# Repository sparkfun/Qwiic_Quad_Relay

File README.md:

SparkFun Qwiic Quad Relay
========================================

[*SparkFun Qwiic Quad Relay (COM-16566)*](https://www.sparkfun.com/products/16566)

The Qwiic Quad Relay is a product designed for switching not one, but **four** high powered devices, from your Arduino or other low powered microcontroller using I<sup>2</sup>C. It's rocking four [relays](https://www.sparkfun.com/products/100) on its' PCB rated up to 5 Amps per channel at 250VAC. Each channel is sporting its own colored LED and silk for easy identification, and has screw terminals for easy connection.  

The board is made to integrate easily into the [Qwiic environment](https://www.sparkfun.com/qwiic) with Qwiic connectors on each side for easy daisy chaining. At the heart of the product is an ATtiny84 with its own I<sup>2</sup>C address awaiting for I<sup>2</sup>C commands that are designated to turn on and off individual channels or _all_ the channels at once! All of this is detailed nicely in provided example code, which also walks you through changing the boards single I<sup>2</sup>C address. There is a four pin header broken out for those of you not taking advantage of the Qwiic connector.

The onboard barrel jack is rated for wall warts in the range, 7-15V but there is a jumper on the underside in the case that your wall wart is 5V. Messing with such high voltage can be dangerous! We've included many safety precautions onto the PCB including, wide traces designed for high amperage, ground isolation between the relay and other circuitry, and a milled out area around the common pin of the relay.

Repository Contents
-------------------

* **/Firmware** - Latest firmware and examples. 
* **/Arduino Example** - Examples on how to use the product with buttons and switches, with hardware interrupts and without.
* **/Hardware** - Eagle design files (.brd, .sch)

Documentation
--------------

* **[Hookup Guide](https://learn.sparkfun.com/tutorials/qwiic-quad-relay-hookup-guide)** - Basic hookup guide

Arduino Library
--------------
* **[SparkFun Qwiic Relay Ardruino Library](https://github.com/sparkfun/SparkFun_Qwiic_Relay_Arduino_Library)** - SparkFun Arduino Library for controlling the Qwiic Single and Quad Relay

License Information
-------------------

This product is _**open source**_! 

Please review the LICENSE.md file for license information. 

If you have any questions or concerns on licensing, please contact technical support on our [SparkFun forums](https://forum.sparkfun.com/viewforum.php?f=152).

Please use, reuse, and modify these files as you see fit. Please maintain attribution to SparkFun Electronics and release under the same license.

Distributed as-is; no warranty is given.

- Your friends at SparkFun.

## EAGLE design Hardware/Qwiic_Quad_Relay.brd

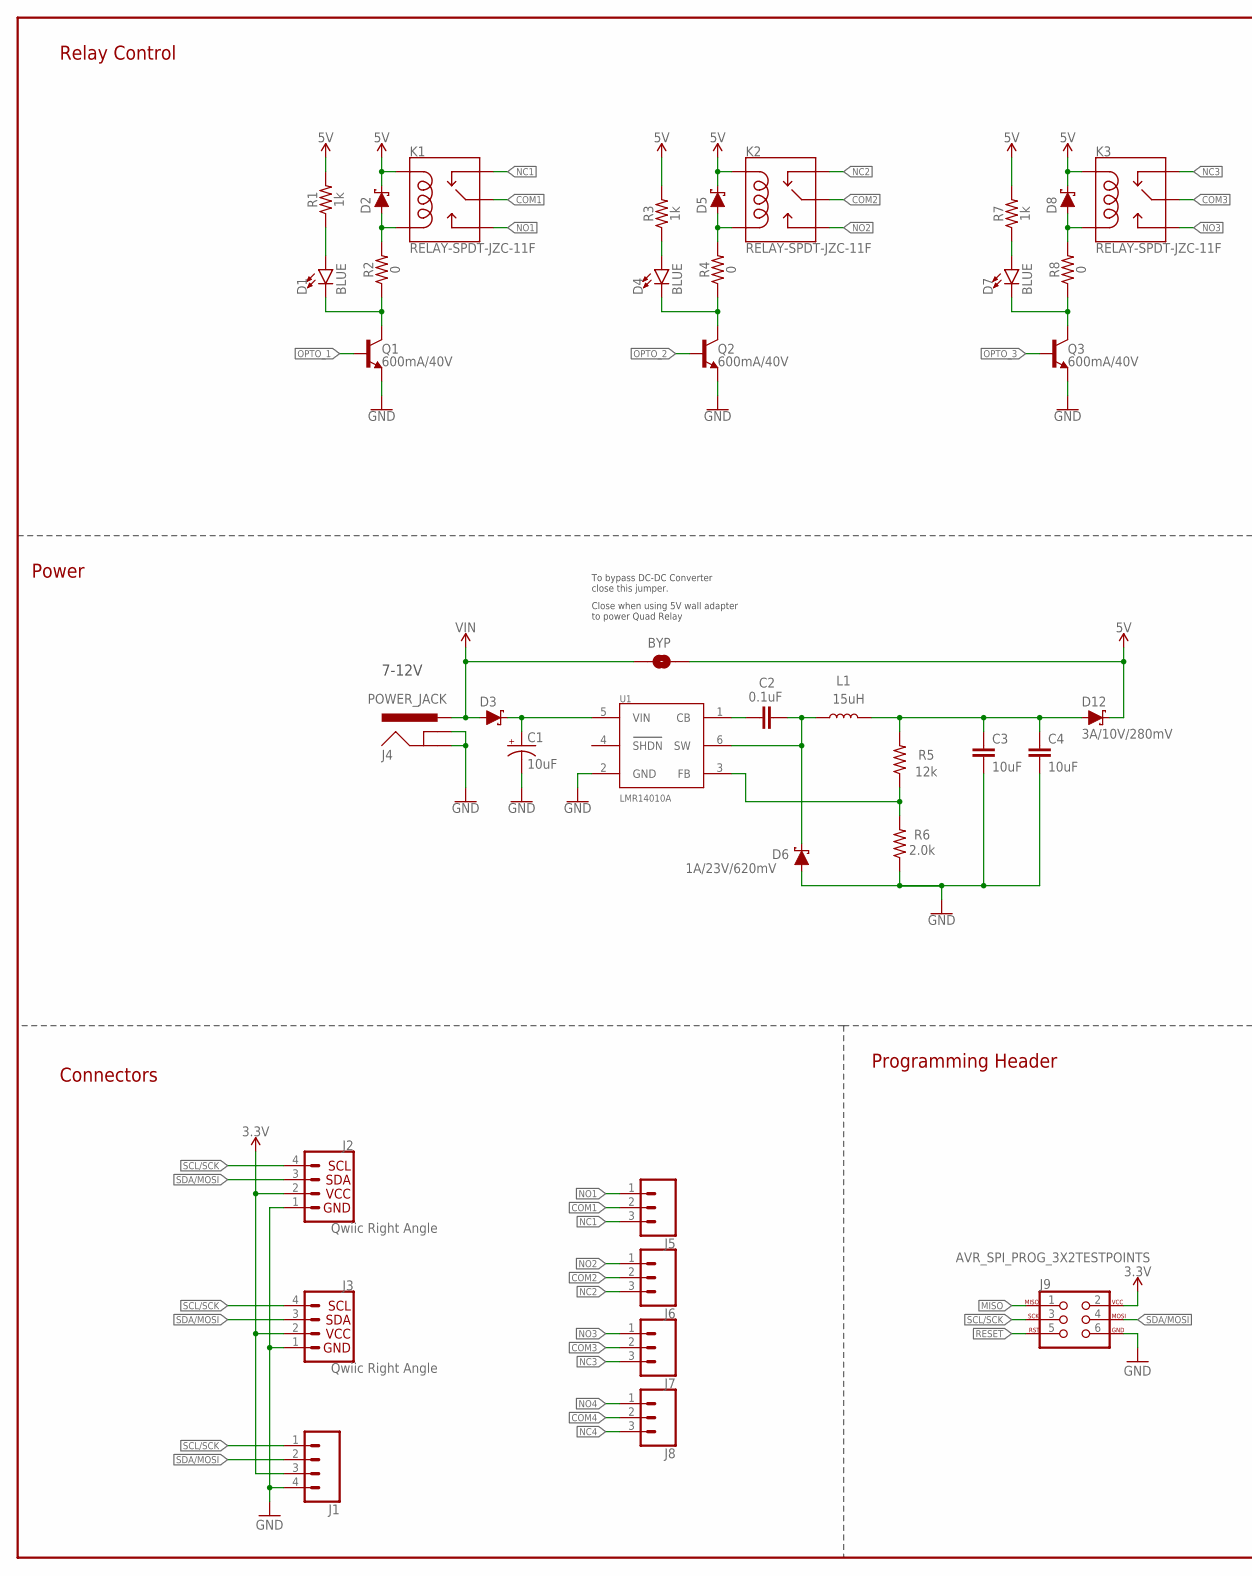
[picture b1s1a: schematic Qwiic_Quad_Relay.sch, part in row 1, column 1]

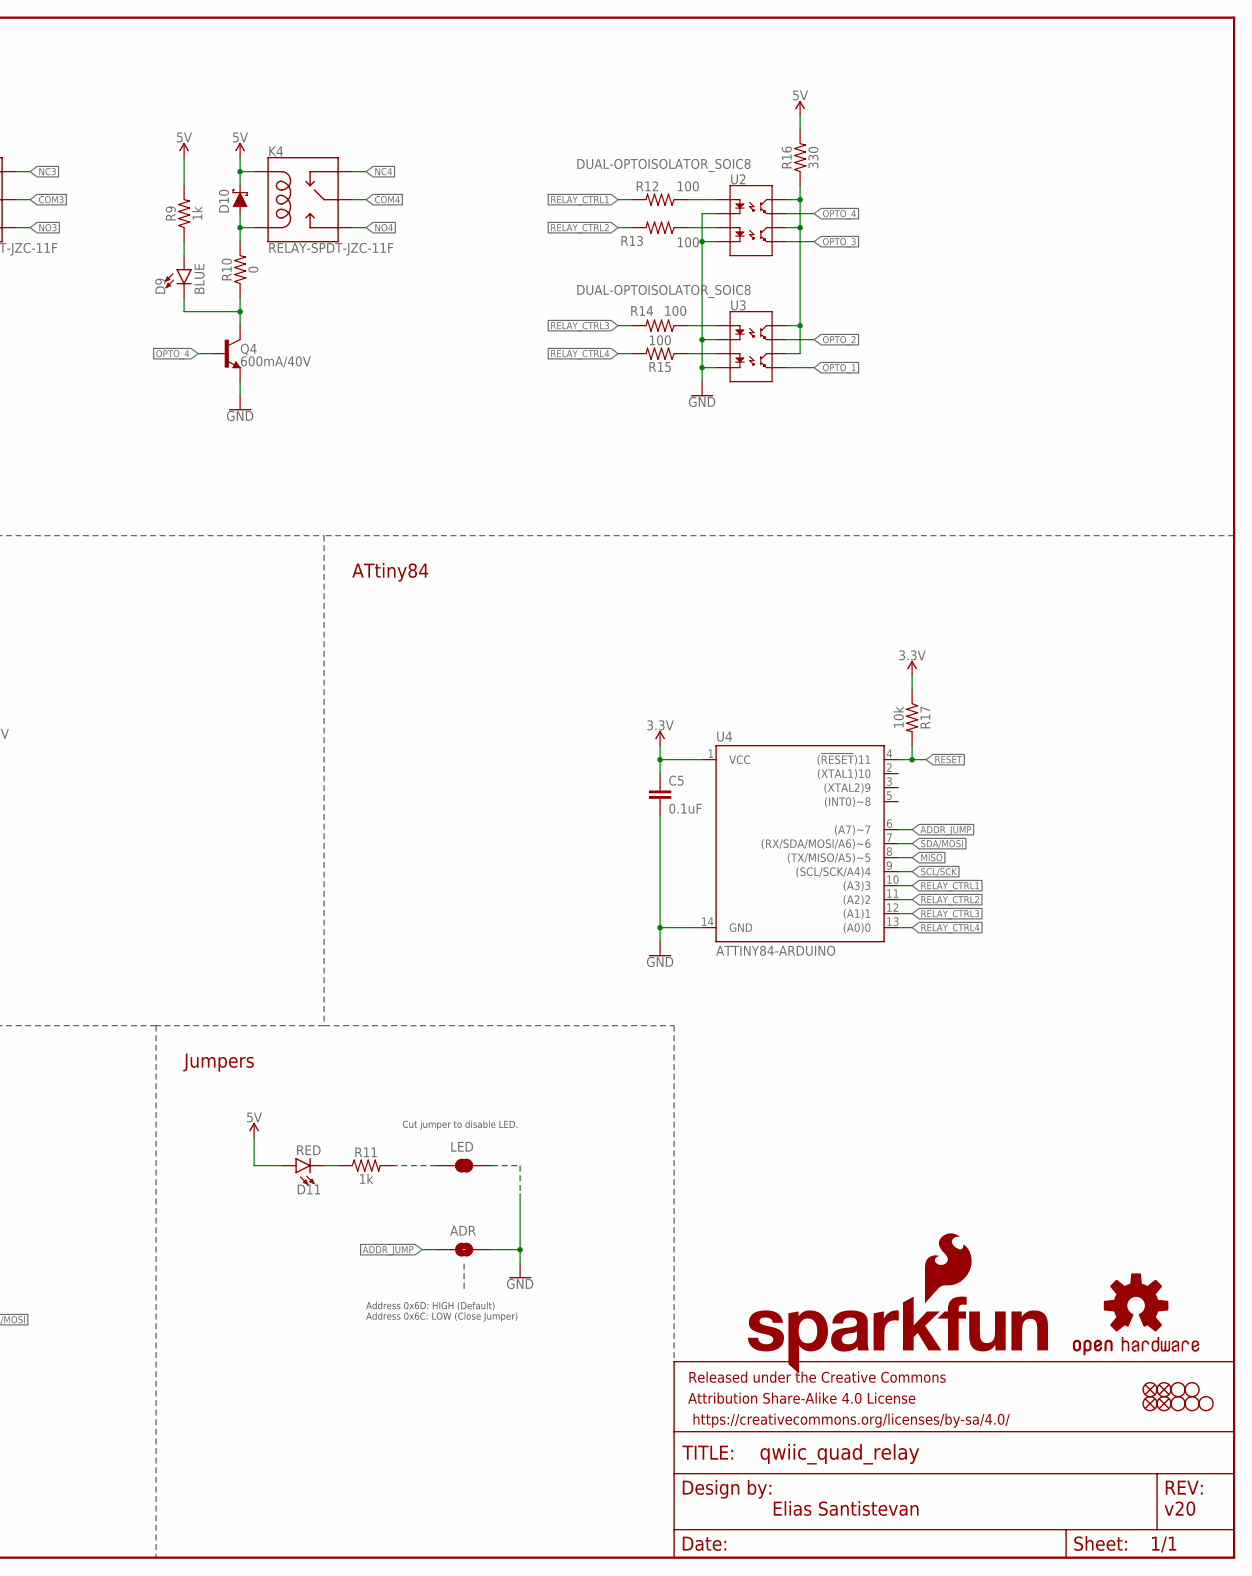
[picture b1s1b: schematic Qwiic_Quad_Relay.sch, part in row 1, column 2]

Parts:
ADR: JUMPER-SMT_2_NO_SILK; SMT-JUMPER_2_NO_SILK
BYP: JUMPER-SMT_2_NO_SILK; SMT-JUMPER_2_NO_SILK
C1: 10uF; EIA3528
C2: 0.1uF; 0402
C3, C4: 10uF; 0603
C5: 0.1uF; 0603
D1, D4, D7, D9: BLUE; LED-0603
D2, D5, D6, D8, D10: 1A/23V/620mV; SOD-323
D3: 1A/40V/500mV; SMA-DIODE
D11: RED; LED-0603
D12: 3A/10V/280mV; SOD-323
FD1, FD2, FD3, FD4: FIDUCIAL1X2; FIDUCIAL-1X2
FRAME1: FRAME-LEDGER; CREATIVE_COMMONS
J1: CONN_041X04_NO_SILK_NO_POP; 1X04_NO_SILK
J2, J3: Qwiic Right Angle; JST04_1MM_RA
J4: POWER_JACK; POWER_JACK_PTH
J5, J6, J7, J8: CONN_03-SCREW-5MM; SCREWTERMINAL-5MM-3
J9: AVR_SPI_PROG_3X2TESTPOINTS; 2X3_TEST_POINTS
JP1, JP4, JP5, JP6, JP7: STAND-OFF
K1, K2, K3, K4: RELAY-SPDT-JZC-11F; RELAY-JZC
L1: 15uH; INDUCTOR_15UH
LED: JUMPER-SMT_2_NC_TRACE_SILK; SMT-JUMPER_2_NC_TRACE_SILK
LOGO1: SFE_LOGO_NAME_FLAME.1_INCH; SFE_LOGO_NAME_FLAME_.1
LOGO2: OSHW-LOGOS; OSHW-LOGO-S
Q1, Q2, Q3, Q4: 600mA/40V; SOT23-3
R1, R3, R7, R9, R11: 1k; 0603
R2, R4, R8, R10: 0; 0603
R5: 12k; 0603
R6: 2.0k; 0603
R12, R13, R14, R15: 100; 0603
R16: 330; 0603
R17: 10k; 0603
U1: LMR14010A; SOT23-6
U2, U3: DUAL-OPTOISOLATOR_SOIC8; SO08
U4: ATTINY84-ARDUINO; SO14

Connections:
3.3V: C5.1, J1.3, J2.2, J3.2, J9.2, R17.1, U4.1 (VCC)
5V: BYP.2, D2.C, D5.C, D8.C, D10.C, D11.A, D12.C, K1.5 (COIL1), K2.5 (COIL1), K3.5 (COIL1), K4.5 (COIL1), R1.2, R3.2, R7.2, R9.2, R16.2
5V_OUT: C3.1, C4.1, D12.A, L1.P2 (2), R5.2
!RESET: J9.5, R17.2, U4.4 ((!RESET!)11)
ADDR_JUMP: ADR.1, U4.6 ((A7)~7)
CB: C2.1, U1.1 (CB)
COM1: J5.2, K1.4 (MAIN)
COM2: J6.2, K2.4 (MAIN)
COM3: J7.2, K3.4 (MAIN)
COM4: J8.2, K4.4 (MAIN)
FB: R5.1, R6.2, U1.3 (FB)
GND: ADR.2, C1.C (-), C3.2, C4.2, C5.2, D6.A, J1.4, J2.1, J3.1, J4.GND, J4.GNDBREAK, J9.6, LED.1, Q1.2 (E), Q2.2 (E), Q3.2 (E), Q4.2 (E), R6.1, U1.2 (GND), U2.2 (C1), U2.4 (C2), U3.2 (C1), U3.4 (C2), U4.14 (GND)
MISO: J9.1, U4.8 ((TX/MISO/A5)~5)
unnamed: D1.A, R1.1
unnamed: D1.C, Q1.3 (C), R2.1
unnamed: R15.1, U3.3 (A2)
unnamed: D4.A, R3.1
unnamed: R14.1, U3.1 (A1)
unnamed: R16.1, U2.6 (CL2), U2.8 (CL1), U3.6 (CL2), U3.8 (CL1)
unnamed: D7.A, R7.1
unnamed: D9.A, R9.1
unnamed: R12.1, U2.1 (A1)
unnamed: D2.A, K1.1 (COIL2), R2.2
unnamed: R13.1, U2.3 (A2)
unnamed: D4.C, Q2.3 (C), R4.1
unnamed: D11.C, R11.1
unnamed: LED.2, R11.2
unnamed: D7.C, Q3.3 (C), R8.1
unnamed: D9.C, Q4.3 (C), R10.1
unnamed: D5.A, K2.1 (COIL2), R4.2
unnamed: D8.A, K3.1 (COIL2), R8.2
unnamed: D10.A, K4.1 (COIL2), R10.2
NC1: J5.3, K1.2 (NC)
NC2: J6.3, K2.2 (NC)
NC3: J7.3, K3.2 (NC)
NC4: J8.3, K4.2 (NC)
NO1: J5.1, K1.3 (NO)
NO2: J6.1, K2.3 (NO)
NO3: J7.1, K3.3 (NO)
NO4: J8.1, K4.3 (NO)
OPTO_1: Q1.1 (B), U3.5 (EM2)
OPTO_2: Q2.1 (B), U3.7 (EM1)
OPTO_3: Q3.1 (B), U2.5 (EM2)
OPTO_4: Q4.1 (B), U2.7 (EM1)
RELAY_CTRL1: R12.2, U4.10 ((A3)3)
RELAY_CTRL2: R13.2, U4.11 ((A2)2)
RELAY_CTRL3: R14.2, U4.12 ((A1)1)
RELAY_CTRL4: R15.2, U4.13 ((A0)0)
SCL/SCK: J1.1, J2.4, J3.4, J9.3, U4.9 ((SCL/SCK/A4)4)
SDA/MOSI: J1.2, J2.3, J3.3, J9.4, U4.7 ((RX/SDA/MOSI/A6)~6)
SW: C2.2, D6.C, L1.P1 (1), U1.6 (SW)
VIN: BYP.1, D3.A, J4.PWR
VIN_DC_DC: C1.A (+), D3.C, U1.5 (VIN)

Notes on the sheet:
Elias Santistevan
v20
Relay Control
Connectors
ATtiny84
Programming Header
Power
Address 0x6D: HIGH (Default) Address 0x6C: LOW (Close Jumper)
7-12V
Cut jumper to disable LED.
Jumpers
To bypass DC-DC Converter close this jumper.
Close when using 5V wall adapter to power Quad Relay

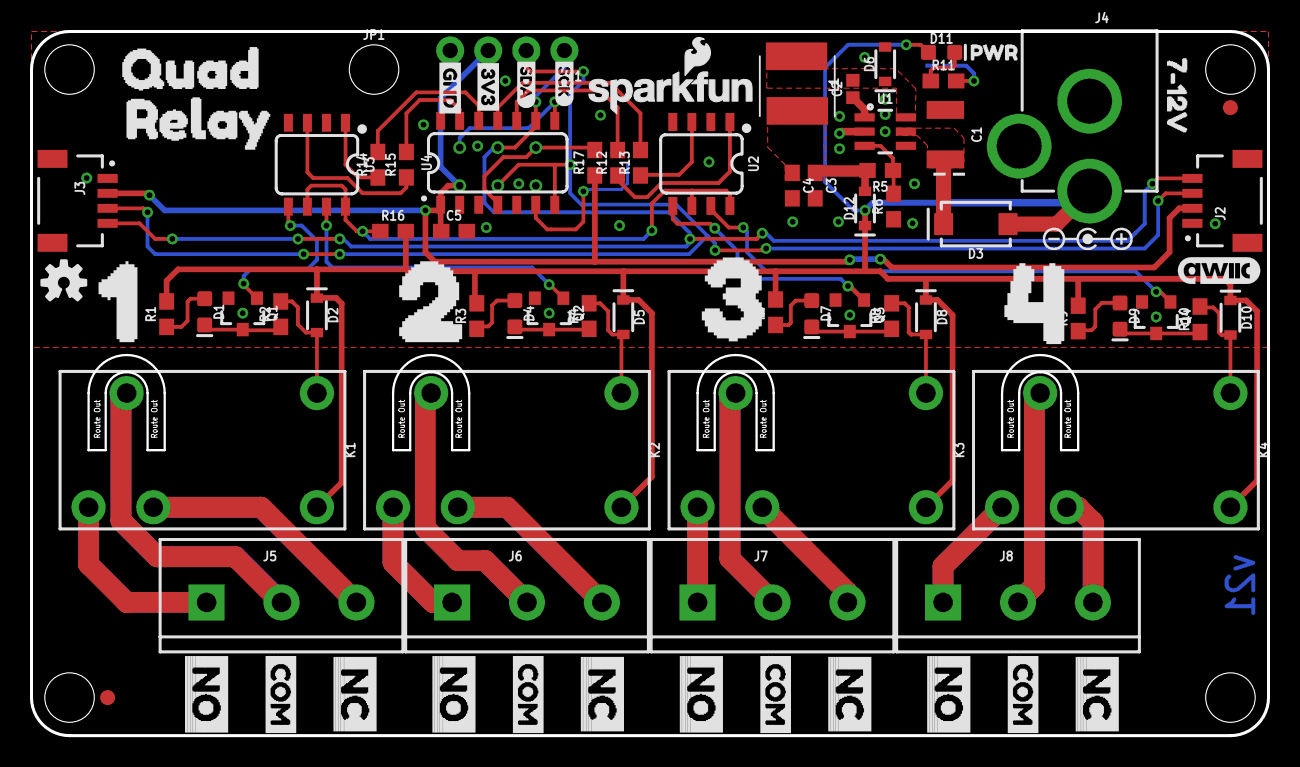
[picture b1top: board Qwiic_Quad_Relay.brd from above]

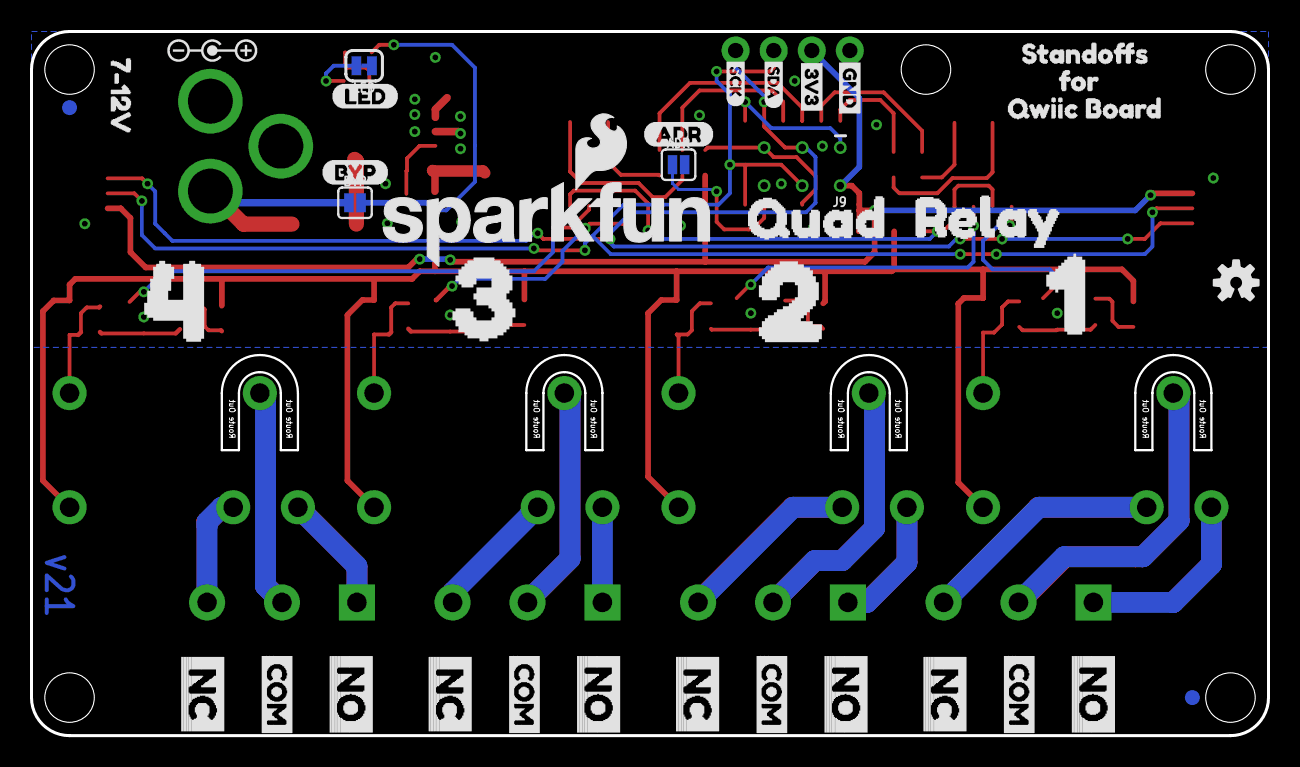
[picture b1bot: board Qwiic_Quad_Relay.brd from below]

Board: 2 copper layers, 82.5 x 47.0 mm, 129 parts (38 on the bottom side), 53 nets.

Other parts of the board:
U$1, U$49: 7#12V0
U$2, U$40: 20
U$3, U$39: 10
U$4, U$41: 30
U$5, U$42: 40
U$6, U$43: QUAD0
U$7, U$44: RELAY0
U$8, U$48: SCK-[)-03
U$9, U$45: GND-03
U$10, U$12: 3V3-03
U$11, U$47: SDA0
U$13: OSHW-LOGO-S
U$14: BYP
U$15, U$18, U$21, U$24, U$27, U$30, U$33, U$36: NO0
U$16, U$19, U$22, U$25, U$28, U$31, U$34, U$37: COM0
U$17, U$20, U$23, U$26, U$29, U$32, U$35, U$38: NC0
U$46: PWR_TO
U$50: STANDOFFS0
U$51, U$54: POLARITY_MARKING_CENTER_POSITIVE#JPG
U$52: FOR1
U$53: LED
U$55: QWIIC_5.5MM
U$56: ADR-()-04
U$57: SFE_LOGO_NAME_FLAME_.2
U$58: QWIIC_BOARD2

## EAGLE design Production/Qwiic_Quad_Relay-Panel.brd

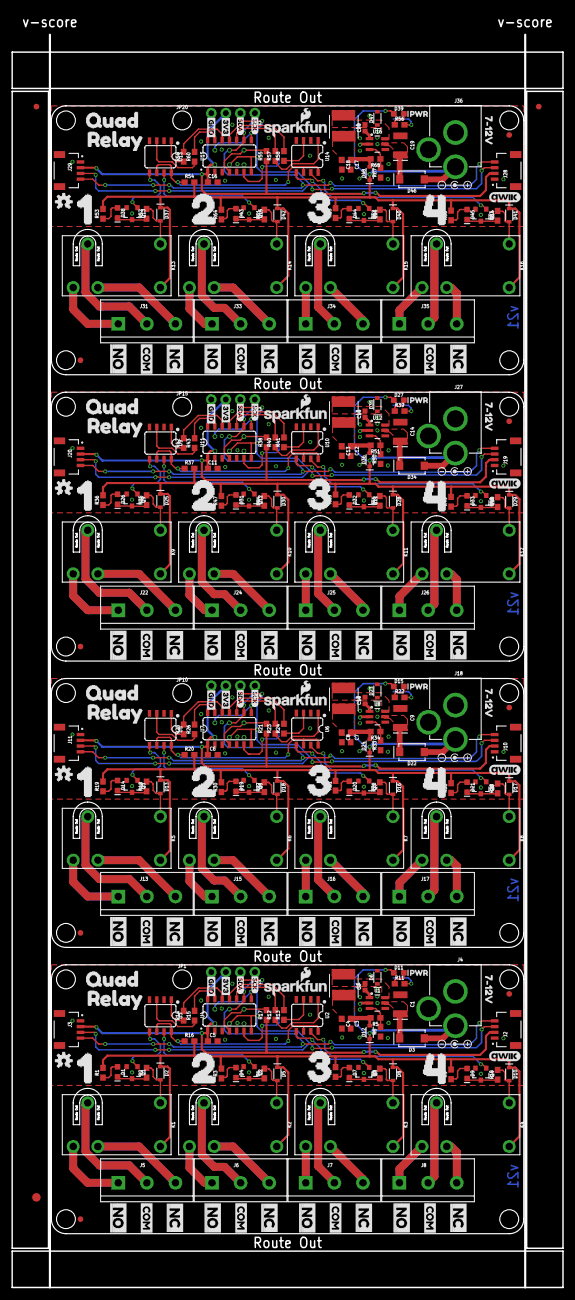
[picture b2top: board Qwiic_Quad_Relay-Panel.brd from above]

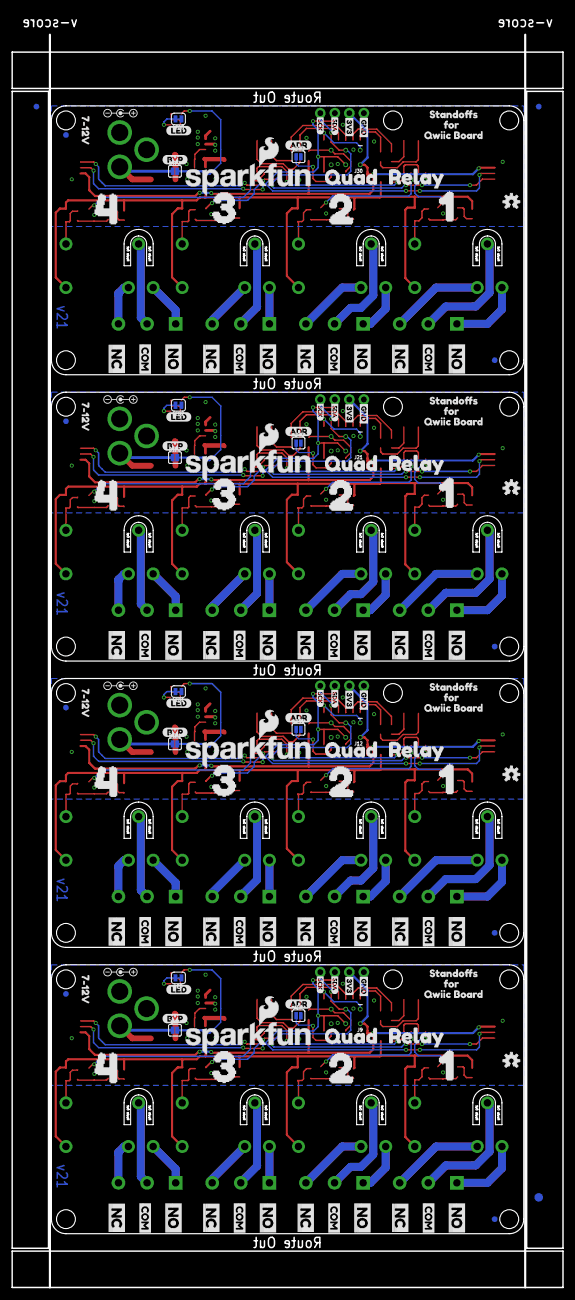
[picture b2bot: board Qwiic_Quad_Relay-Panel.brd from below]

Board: 2 copper layers, 96.1 x 222.8 mm, 518 parts (155 on the bottom side), 212 nets.

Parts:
ADR, ADR1, ADR2, ADR3: JUMPER-SMT_2_NO_SILK; SMT-JUMPER_2_NO_SILK
BYP, BYP1, BYP2, BYP3: JUMPER-SMT_2_NO_SILK; SMT-JUMPER_2_NO_SILK
C1, C9, C14, C19: 10uF; EIA3528
C2, C10, C15, C20: 0.1uF; 0402
C3, C4, C7, C8, C12, C13, C17, C18: 10uF; 0603
C5, C6, C11, C16: 0.1uF; 0603
D1, D4, D7, D9, D14, D19, D20, D21, D26, D31, D32, D33, D38, D43, D44, D45: BLUE; LED-0603
D2, D5, D6, D8, D10, D13, D16, D17, D18, D23, D25, D28, D29, D30, D35, D37, D40, D41, D42, D47: 1A/23V/620mV; SOD-323
D3, D22, D34, D46: 1A/40V/500mV; SMA-DIODE
D11, D15, D27, D39: RED; LED-0603
D12, D24, D36, D48: 3A/10V/280mV; SOD-323
E$1, E$2, E$3, E$4: FIDUCIAL-1X2
E$5, E$6: FIDUCIAL-1.5X3
FD1, FD2, FD3, FD4, FD5, FD6, FD7, FD8, FD9, FD10, FD11, FD12, FD13, FD14, FD15, FD16: FIDUCIAL1X2; FIDUCIAL-1X2
J1, J14, J23, J32: 1X04_NO_SILK
J2, J3, J10, J11, J19, J20, J28, J29: Qwiic Right Angle; JST04_1MM_RA
J4, J18, J27, J36: POWER_JACK; POWER_JACK_PTH
J5, J6, J7, J8, J13, J15, J16, J17, J22, J24, J25, J26, J31, J33, J34, J35: SCREWTERMINAL-5MM-3
J9, J12, J21, J30: AVR_SPI_PROG_3X2TESTPOINTS; 2X3_TEST_POINTS
JP1, JP2, JP3, JP4, JP5, JP6, JP7, JP8, JP9, JP10, JP11, JP12, JP13, JP14, JP15, JP16, JP17, JP18, JP19, JP20: STAND-OFF
K1, K2, K3, K4, K5, K6, K7, K8, K9, K10, K11, K12, K13, K14, K15, K16: RELAY-SPDT-JZC-11F; RELAY-JZC
L1, L2, L3, L4: 15uH; INDUCTOR_15UH
LED, LED1, LED2, LED3: JUMPER-SMT_2_NC_TRACE_SILK; SMT-JUMPER_2_NC_TRACE_SILK
LOGO1, LOGO4, LOGO6, LOGO8: SFE_LOGO_NAME_FLAME.1_INCH; SFE_LOGO_NAME_FLAME_.1
LOGO2, LOGO3, LOGO5, LOGO7: OSHW-LOGOS; OSHW-LOGO-S
Q1, Q2, Q3, Q4, Q5, Q6, Q7, Q8, Q9, Q10, Q11, Q12, Q13, Q14, Q15, Q16: 600mA/40V; SOT23-3
R1, R3, R7, R9, R11, R19, R22, R30, R31, R32, R36, R39, R47, R48, R49, R53, R56, R64, R65, R66: 1k; 0603
R2, R4, R8, R10, R18, R27, R28, R29, R35, R44, R45, R46, R52, R61, R62, R63: 0; 0603
R5, R34, R51, R68: 12k; 0603
R6, R33, R50, R67: 2.0k; 0603
R12, R13, R14, R15, R23, R24, R25, R26, R40, R41, R42, R43, R57, R58, R59, R60: 100; 0603
R16, R20, R37, R54: 330; 0603
R17, R21, R38, R55: 10k; 0603
U1, U8, U12, U16: LMR14010A; SOT23-6
U2, U3, U5, U6, U9, U10, U13, U14: DUAL-OPTOISOLATOR_SOIC8; SO08
U4, U7, U11, U15: ATTINY84-ARDUINO; SO14
U$1, U$49, U$107, U$108, U$165, U$166, U$223, U$224: 7#12V0
U$2, U$40, U$59, U$89, U$117, U$147, U$175, U$205: 20
U$3, U$39, U$60, U$88, U$118, U$146, U$176, U$204: 10
U$4, U$41, U$61, U$90, U$119, U$148, U$177, U$206: 30
U$5, U$42, U$62, U$91, U$120, U$149, U$178, U$207: 40
U$6, U$43, U$110, U$111, U$168, U$169, U$226, U$227: QUAD0
U$7, U$44, U$63, U$92, U$121, U$150, U$179, U$208: RELAY0
U$8, U$48, U$94, U$99, U$152, U$157, U$210, U$215: SCK-[)-03
U$9, U$45, U$95, U$97, U$153, U$155, U$211, U$213: GND-03
U$10, U$12, U$103, U$104, U$161, U$162, U$219, U$220: 3V3-03
U$11, U$47, U$96, U$98, U$154, U$156, U$212, U$214: SDA0
U$13, U$93, U$151, U$209: OSHW-LOGO-S
U$14, U$105, U$163, U$221: BYP
U$15, U$18, U$21, U$24, U$27, U$30, U$33, U$36, U$64, U$67, U$70, U$73, U$76, U$79, U$82, U$85, U$122, U$125, U$128, U$131, U$134, U$137, U$140, U$143, U$180, U$183, U$186, U$189, U$192, U$195, U$198, U$201: NO0
U$16, U$19, U$22, U$25, U$28, U$31, U$34, U$37, U$65, U$68, U$71, U$74, U$77, U$80, U$83, U$86, U$123, U$126, U$129, U$132, U$135, U$138, U$141, U$144, U$181, U$184, U$187, U$190, U$193, U$196, U$199, U$202: COM0
U$17, U$20, U$23, U$26, U$29, U$32, U$35, U$38, U$66, U$69, U$72, U$75, U$78, U$81, U$84, U$87, U$124, U$127, U$130, U$133, U$136, U$139, U$142, U$145, U$182, U$185, U$188, U$191, U$194, U$197, U$200, U$203: NC0
U$46, U$106, U$164, U$222: PWR_TO
U$50, U$114, U$172, U$230: STANDOFFS0
U$51, U$54, U$100, U$101, U$158, U$159, U$216, U$217: POLARITY_MARKING_CENTER_POSITIVE#JPG
U$52, U$115, U$173, U$231: FOR1
U$53, U$112, U$170, U$228: LED
U$55, U$109, U$167, U$225: QWIIC_5.5MM
U$56, U$102, U$160, U$218: ADR-()-04
U$57, U$113, U$171, U$229: SFE_LOGO_NAME_FLAME_.2
U$58, U$116, U$174, U$232: QWIIC_BOARD2

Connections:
3.3V: C5.1, J1.3, J2.2, J3.2, J9.2, R17.1, U4.1
3.3V1: C6.1, J10.2, J11.2, J12.2, J14.3, R21.1, U7.1
3.3V2: C11.1, J19.2, J20.2, J21.2, J23.3, R38.1, U11.1
3.3V3: C16.1, J28.2, J29.2, J30.2, J32.3, R55.1, U15.1
5V: BYP.2, D2.C, D5.C, D8.C, D10.C, D11.A, D12.C, K1.5, K2.5, K3.5, K4.5, R1.2, R3.2, R7.2, R9.2, R16.2
5V1: BYP1.2, D13.C, D15.A, D16.C, D17.C, D18.C, D24.C, K5.5, K6.5, K7.5, K8.5, R19.2, R20.2, R30.2, R31.2, R32.2
5V2: BYP2.2, D25.C, D27.A, D28.C, D29.C, D30.C, D36.C, K9.5, K10.5, K11.5, K12.5, R36.2, R37.2, R47.2, R48.2, R49.2
5V3: BYP3.2, D37.C, D39.A, D40.C, D41.C, D42.C, D48.C, K13.5, K14.5, K15.5, K16.5, R53.2, R54.2, R64.2, R65.2, R66.2
5V_OUT: C3.1, C4.1, D12.A, L1.P2, R5.2
5V_OUT1: C7.1, C8.1, D24.A, L2.P2, R34.2
5V_OUT2: C12.1, C13.1, D36.A, L3.P2, R51.2
5V_OUT3: C17.1, C18.1, D48.A, L4.P2, R68.2
!RESET: J9.5, R17.2, U4.4
!RESET1: J12.5, R21.2, U7.4
!RESET2: J21.5, R38.2, U11.4
!RESET3: J30.5, R55.2, U15.4
ADDR_JUMP: ADR.1, U4.6
ADDR_JUMP1: ADR1.1, U7.6
ADDR_JUMP2: ADR2.1, U11.6
ADDR_JUMP3: ADR3.1, U15.6
CB: C2.1, U1.1
CB1: C10.1, U8.1
CB2: C15.1, U12.1
CB3: C20.1, U16.1
COM1: J5.2, K1.4
COM2: J6.2, K2.4
COM3: J7.2, K3.4
COM4: J8.2, K4.4
COM5: J13.2, K5.4
COM6: J15.2, K6.4
COM7: J16.2, K7.4
COM8: J17.2, K8.4
COM9: J22.2, K9.4
COM10: J24.2, K10.4
COM11: J25.2, K11.4
COM12: J26.2, K12.4
COM13: J31.2, K13.4
COM14: J33.2, K14.4
COM15: J34.2, K15.4
COM16: J35.2, K16.4
FB: R5.1, R6.2, U1.3
FB1: R33.2, R34.1, U8.3
FB2: R50.2, R51.1, U12.3
FB3: R67.2, R68.1, U16.3
GND: ADR.2, C1.C, C3.2, C4.2, C5.2, D6.A, J1.4, J2.1, J3.1, J4.GND, J4.GNDBREAK, J9.6, LED.1, Q1.2, Q2.2, Q3.2, Q4.2, R6.1, U1.2, U2.2, U2.4, U3.2, U3.4, U4.14
GND1: ADR1.2, C6.2, C7.2, C8.2, C9.C, D23.A, J10.1, J11.1, J12.6, J14.4, J18.GND, J18.GNDBREAK, LED1.1, Q5.2, Q6.2, Q7.2, Q8.2, R33.1, U5.2, U5.4, U6.2, U6.4, U7.14, U8.2
GND2: ADR2.2, C11.2, C12.2, C13.2, C14.C, D35.A, J19.1, J20.1, J21.6, J23.4, J27.GND, J27.GNDBREAK, LED2.1, Q9.2, Q10.2, Q11.2, Q12.2, R50.1, U9.2, U9.4, U10.2, U10.4, U11.14, U12.2
GND3: ADR3.2, C16.2, C17.2, C18.2, C19.C, D47.A, J28.1, J29.1, J30.6, J32.4, J36.GND, J36.GNDBREAK, LED3.1, Q13.2, Q14.2, Q15.2, Q16.2, R67.1, U13.2, U13.4, U14.2, U14.4, U15.14, U16.2
MISO: J9.1, U4.8
MISO1: J12.1, U7.8
MISO2: J21.1, U11.8
MISO3: J30.1, U15.8
unnamed: D1.A, R1.1
unnamed: D1.C, Q1.3, R2.1
unnamed: R15.1, U3.3
unnamed: D4.A, R3.1
unnamed: R14.1, U3.1
unnamed: R16.1, U2.6, U2.8, U3.6, U3.8
unnamed: D7.A, R7.1
unnamed: D9.A, R9.1
unnamed: R12.1, U2.1
unnamed: D2.A, K1.1, R2.2
unnamed: R13.1, U2.3
unnamed: D4.C, Q2.3, R4.1
unnamed: D11.C, R11.1
unnamed: LED.2, R11.2
unnamed: D7.C, Q3.3, R8.1
unnamed: D14.C, Q5.3, R18.1
unnamed: D9.C, Q4.3, R10.1
unnamed: D5.A, K2.1, R4.2
unnamed: D15.C, R22.1
unnamed: R26.1, U5.3
unnamed: R25.1, U5.1
unnamed: R20.1, U5.6, U5.8, U6.6, U6.8
unnamed: D8.A, K3.1, R8.2
unnamed: D10.A, K4.1, R10.2
unnamed: R23.1, U6.1
unnamed: R24.1, U6.3
unnamed: D19.C, Q8.3, R27.1
unnamed: D20.C, Q7.3, R28.1
unnamed: D21.C, Q6.3, R29.1
unnamed: D13.A, K5.1, R18.2
unnamed: D18.A, K6.1, R27.2
unnamed: D16.A, K7.1, R28.2
unnamed: D17.A, K8.1, R29.2
unnamed: LED1.2, R22.2
unnamed: D14.A, R19.1
unnamed: D19.A, R30.1
unnamed: D20.A, R31.1
unnamed: D21.A, R32.1
unnamed: D26.C, Q9.3, R35.1
unnamed: D27.C, R39.1
unnamed: R43.1, U9.3
unnamed: R42.1, U9.1
unnamed: R37.1, U9.6, U9.8, U10.6, U10.8
unnamed: R40.1, U10.1
unnamed: R41.1, U10.3
unnamed: D31.C, Q12.3, R44.1
unnamed: D32.C, Q11.3, R45.1
unnamed: D33.C, Q10.3, R46.1
unnamed: D25.A, K9.1, R35.2
unnamed: D30.A, K10.1, R44.2
unnamed: D28.A, K11.1, R45.2
unnamed: D29.A, K12.1, R46.2
unnamed: LED2.2, R39.2
unnamed: D26.A, R36.1
unnamed: D31.A, R47.1
unnamed: D32.A, R48.1
unnamed: D33.A, R49.1
unnamed: D38.C, Q13.3, R52.1
unnamed: D39.C, R56.1
unnamed: R60.1, U13.3
unnamed: R59.1, U13.1
unnamed: R54.1, U13.6, U13.8, U14.6, U14.8
unnamed: R57.1, U14.1
unnamed: R58.1, U14.3
unnamed: D43.C, Q16.3, R61.1
unnamed: D44.C, Q15.3, R62.1
unnamed: D45.C, Q14.3, R63.1
unnamed: D37.A, K13.1, R52.2
unnamed: D42.A, K14.1, R61.2
unnamed: D40.A, K15.1, R62.2
unnamed: D41.A, K16.1, R63.2
unnamed: LED3.2, R56.2
unnamed: D38.A, R53.1
unnamed: D43.A, R64.1
unnamed: D44.A, R65.1
unnamed: D45.A, R66.1
NC1: J5.3, K1.2
NC2: J6.3, K2.2
NC3: J7.3, K3.2
NC4: J8.3, K4.2
NC5: J13.3, K5.2
NC6: J15.3, K6.2
NC7: J16.3, K7.2
NC8: J17.3, K8.2
NC9: J22.3, K9.2
NC10: J24.3, K10.2
NC11: J25.3, K11.2
NC12: J26.3, K12.2
NC13: J31.3, K13.2
NC14: J33.3, K14.2
NC15: J34.3, K15.2
NC16: J35.3, K16.2
NO1: J5.1, K1.3
NO2: J6.1, K2.3
NO3: J7.1, K3.3
NO4: J8.1, K4.3
NO5: J13.1, K5.3
NO6: J15.1, K6.3
NO7: J16.1, K7.3
NO8: J17.1, K8.3
NO9: J22.1, K9.3
NO10: J24.1, K10.3
NO11: J25.1, K11.3
NO12: J26.1, K12.3
NO13: J31.1, K13.3
NO14: J33.1, K14.3
NO15: J34.1, K15.3
NO16: J35.1, K16.3
OPTO_1: Q1.1, U3.5
OPTO_2: Q2.1, U3.7
OPTO_3: Q3.1, U2.5
OPTO_4: Q4.1, U2.7
OPTO_5: Q5.1, U5.5
OPTO_6: Q8.1, U5.7
OPTO_7: Q7.1, U6.5
OPTO_8: Q6.1, U6.7
OPTO_9: Q9.1, U9.5
OPTO_10: Q12.1, U9.7
OPTO_11: Q11.1, U10.5
OPTO_12: Q10.1, U10.7
OPTO_13: Q13.1, U13.5
OPTO_14: Q16.1, U13.7
OPTO_15: Q15.1, U14.5
OPTO_16: Q14.1, U14.7
RELAY_CTRL1: R12.2, U4.10
RELAY_CTRL2: R13.2, U4.11
RELAY_CTRL3: R14.2, U4.12
RELAY_CTRL4: R15.2, U4.13
RELAY_CTRL5: R23.2, U7.10
RELAY_CTRL6: R24.2, U7.11
RELAY_CTRL7: R25.2, U7.12
RELAY_CTRL8: R26.2, U7.13
RELAY_CTRL9: R40.2, U11.10
RELAY_CTRL10: R41.2, U11.11
RELAY_CTRL11: R42.2, U11.12
RELAY_CTRL12: R43.2, U11.13
RELAY_CTRL13: R57.2, U15.10
RELAY_CTRL14: R58.2, U15.11
RELAY_CTRL15: R59.2, U15.12
RELAY_CTRL16: R60.2, U15.13
SCL/SCK: J1.1, J2.4, J3.4, J9.3, U4.9
SCL/SCK1: J10.4, J11.4, J12.3, J14.1, U7.9
SCL/SCK2: J19.4, J20.4, J21.3, J23.1, U11.9
SCL/SCK3: J28.4, J29.4, J30.3, J32.1, U15.9
SDA/MOSI: J1.2, J2.3, J3.3, J9.4, U4.7
SDA/MOSI1: J10.3, J11.3, J12.4, J14.2, U7.7
SDA/MOSI2: J19.3, J20.3, J21.4, J23.2, U11.7
SDA/MOSI3: J28.3, J29.3, J30.4, J32.2, U15.7
SW: C2.2, D6.C, L1.P1, U1.6
SW1: C10.2, D23.C, L2.P1, U8.6
SW2: C15.2, D35.C, L3.P1, U12.6
SW3: C20.2, D47.C, L4.P1, U16.6
VIN: BYP.1, D3.A, J4.PWR
VIN1: BYP1.1, D22.A, J18.PWR
VIN2: BYP2.1, D34.A, J27.PWR
VIN3: BYP3.1, D46.A, J36.PWR
VIN_DC_DC: C1.A, D3.C, U1.5
VIN_DC_DC1: C9.A, D22.C, U8.5
VIN_DC_DC2: C14.A, D34.C, U12.5
VIN_DC_DC3: C19.A, D46.C, U16.5

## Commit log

2018-11-13 Updated to v10 and updated example code that adds commented out line for second i2c address
2018-11-15 Reduces current consumption on every relay channel, seperates 3.3V and 5V system
    *Current consumption:
    -10 Ohm coil resistor changed to 33 Ohm
    -220 Ohm reistor into base of NPN changed to 330
    *3.3V Qwiic System:
    -Put ATtiny84 back onto the 3.3V Qwiic System
    -Changed OptoIsolator resistors from 220 Ohm to 100 Ohm to hit current requirements
2018-11-15 Adds selective soldering path to documents layer
2018-11-19 Changed route out layer from milling to Dimension
2018-11-21 panel
2018-12-14 Changes fuses to add brown out detection
2019-07-02 Removes Example Code from Hardware library which has been moved to SparkFun Qwiic Relay Arduino Library
2019-07-02 Fixes Readme image and puts link to Arduino library, also in README
2019-07-02 Adds exclamation point necessary for image
2019-07-02 Fixes some more issues I just made
2019-07-02 Updates the text on the Arduino library
2020-04-06 Moves 33 Ohm resistor to after the coil so that drop doesn't occur before it.
2020-04-06 Adds circuitry for DC-DC converter (no traces routed)
2020-04-07 Re-adds dc-dc converter circuitry - somehow it was not in the last push
2020-04-07 Routes new circuitry
2020-04-07 Fixes various minor DRC issues
2020-04-07 Adds polygons for switch pin and VIN
2020-04-08 Updates inductor with inductor with correct amperage rating
2020-04-08 Adjusts silk, add bypass jumper, corrects feedback pin resistor values -> output: 5.35V
2020-04-08 Updates schematic
2020-04-08 Adds correct inductor
2020-04-08 Changes standoff to the one used in the SparkFun libraries
2020-04-08 Fixes bypass
2020-04-09 Adds better silk, additional standoff, schotkky diode to protect dc/dc converter circuit
2020-04-09 Fixes inductor
2020-04-09 Adds silk to indicate qwiic board standoffs
2020-04-09 Removes Buzzard lables and old production files
2020-04-09 Adds new panel
2020-05-26 Changes LED jumper to normally closed with trace
2020-05-26 Updates production panel following latest commit
2020-06-30 Replaces 33 Ohm resistors with 0 Ohm
2025-01-24 Replaces clamping diode with something more suitable to stated maximum input voltage of the product.
2025-01-28 Updates version in board to v21
2025-01-28 Rolls version in schematic to v21
2025-01-31 Adds new production panel

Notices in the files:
parts and their libraries:
SparkFun-Capacitors: Licensing: Creative Commons ShareAlike 4.0 International - https://creativecommons.org/licenses/by-sa/4.0
SparkFun-Aesthetics: Released under the Creative Commons Attribution Share-Alike 4.0 License
SparkFun-Aesthetics: https://creativecommons.org/licenses/by-sa/4.0
